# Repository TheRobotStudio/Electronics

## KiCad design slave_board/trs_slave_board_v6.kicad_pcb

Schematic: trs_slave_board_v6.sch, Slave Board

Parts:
C1: 10µF
C2: C
CAN_Transceiver1: SN65HVD232D
K1: CONN_3
MASTER_EPOS2_1: Headers_CONN
MBED_SB_1: mbed_NXP_LPC1768
MUX_1: MUX_CD74HC4067
P1, P2, P6: CONN_4
P3, P4: CONN_6
P5: CONN_10
P7: CONN_8X2
P8, P9: CONN_1
R1: 120
R2: R

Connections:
GND: C1.2, C2.2, CAN_Transceiver1.2, CAN_Transceiver1.8, K1.3, MASTER_EPOS2_1.2, MASTER_EPOS2_1.8, MBED_SB_1.1, MUX_1.12 (GND), P1.1, P1.2, P1.3, P1.4, R2.2
unnamed: MUX_1.4 (CHAN5), P7.6
unnamed: MUX_1.2 (CHAN7), P7.8
unnamed: MUX_1.3 (CHAN6), P7.7
unnamed: MUX_1.5 (CHAN4), P7.5
unnamed: MUX_1.6 (CHAN3), P7.4
unnamed: MUX_1.7 (CHAN2), P7.3
unnamed: MUX_1.22 (CHAN9), P7.10
unnamed: MUX_1.19 (CHAN12), P7.13
unnamed: MUX_1.20 (CHAN11), P7.12
unnamed: MUX_1.21 (CHAN10), P7.11
unnamed: MUX_1.23 (CHAN8), P7.9
unnamed: MBED_SB_1.24, P5.7
unnamed: MBED_SB_1.36, P4.1
unnamed: MBED_SB_1.35, P4.2
unnamed: MBED_SB_1.34, P4.3
unnamed: MBED_SB_1.33, P4.4
unnamed: MBED_SB_1.32, P4.5
unnamed: MBED_SB_1.31, P4.6
unnamed: MBED_SB_1.21, P5.10
unnamed: MBED_SB_1.22, P5.9
unnamed: MBED_SB_1.23, P5.8
unnamed: MBED_SB_1.25, P5.6
unnamed: MBED_SB_1.26, P5.5
unnamed: MUX_1.8 (CHAN1), P7.2
unnamed: MUX_1.9 (CHAN0), P7.1
unnamed: MBED_SB_1.12, P8.1
unnamed: MBED_SB_1.29, MUX_1.11 (S1), P5.2
unnamed: MBED_SB_1.30, MUX_1.10 (S0), P5.1
unnamed: K1.2 (PM), MBED_SB_1.14
unnamed: K1.1, MBED_SB_1.13
unnamed: MUX_1.15 (EN), R2.1
unnamed: MBED_SB_1.27, MUX_1.13 (S3), P5.4
unnamed: MBED_SB_1.28, MUX_1.14 (S2), P5.3
unnamed: MUX_1.16 (CHAN15), P7.16
unnamed: MBED_SB_1.20, P3.6
unnamed: MBED_SB_1.19, P3.5
unnamed: MBED_SB_1.18, P3.4
unnamed: MBED_SB_1.17, P3.3
unnamed: MBED_SB_1.16, P3.2
unnamed: MUX_1.17 (CHAN14), P7.15
unnamed: MUX_1.18 (CHAN13), P7.14
unnamed: MBED_SB_1.15, MUX_1.1 (COM), P3.1
unnamed: MBED_SB_1.39, P9.1
unnamed: CAN_Transceiver1.1, MBED_SB_1.10
unnamed: CAN_Transceiver1.4, MBED_SB_1.9
unnamed: MASTER_EPOS2_1.4, MBED_SB_1.8
unnamed: MASTER_EPOS2_1.7, MBED_SB_1.7
unnamed: MASTER_EPOS2_1.5, MBED_SB_1.6
unnamed: CAN_Transceiver1.6, MASTER_EPOS2_1.10, R1.1
unnamed: MASTER_EPOS2_1.6, MBED_SB_1.11
unnamed: CAN_Transceiver1.7, MASTER_EPOS2_1.9, R1.2
unnamed: C2.1, CAN_Transceiver1.3, MBED_SB_1.40, MUX_1.24 (VCC), P6.1, P6.2, P6.3, P6.4
unnamed: MASTER_EPOS2_1.3, MBED_SB_1.5
unnamed: C1.1, MASTER_EPOS2_1.1, MBED_SB_1.2, P2.1, P2.2, P2.3, P2.4

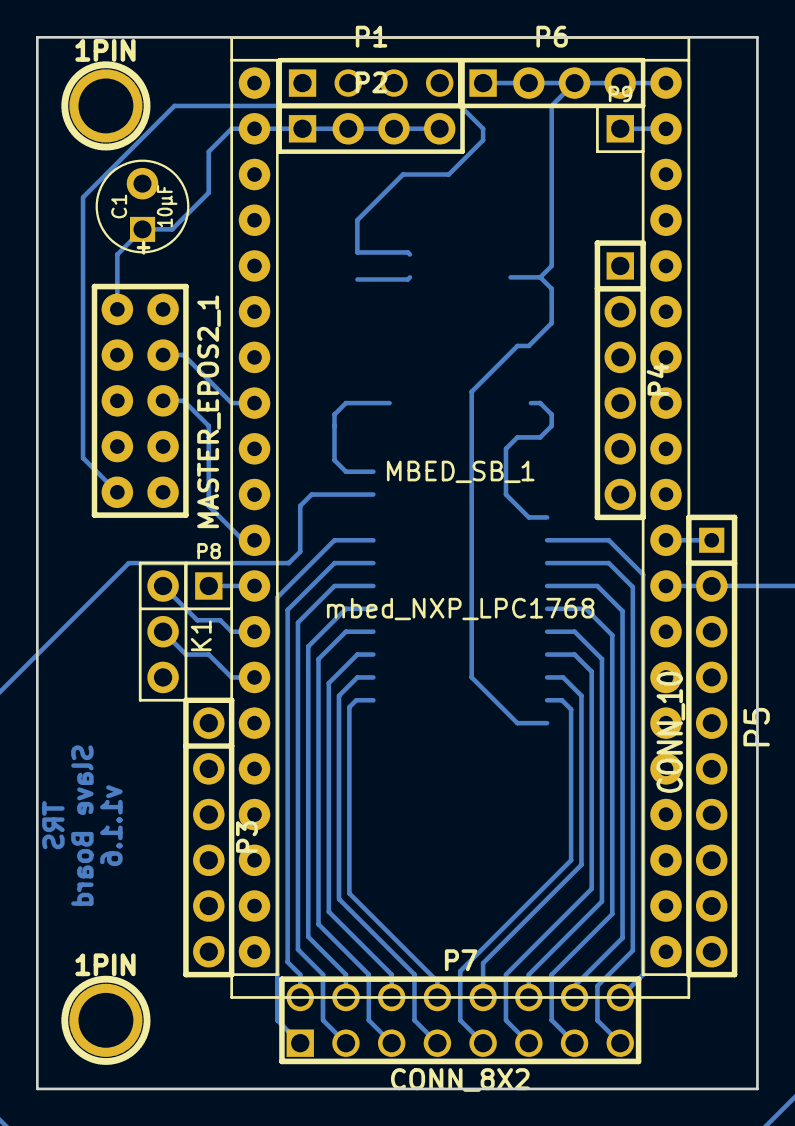
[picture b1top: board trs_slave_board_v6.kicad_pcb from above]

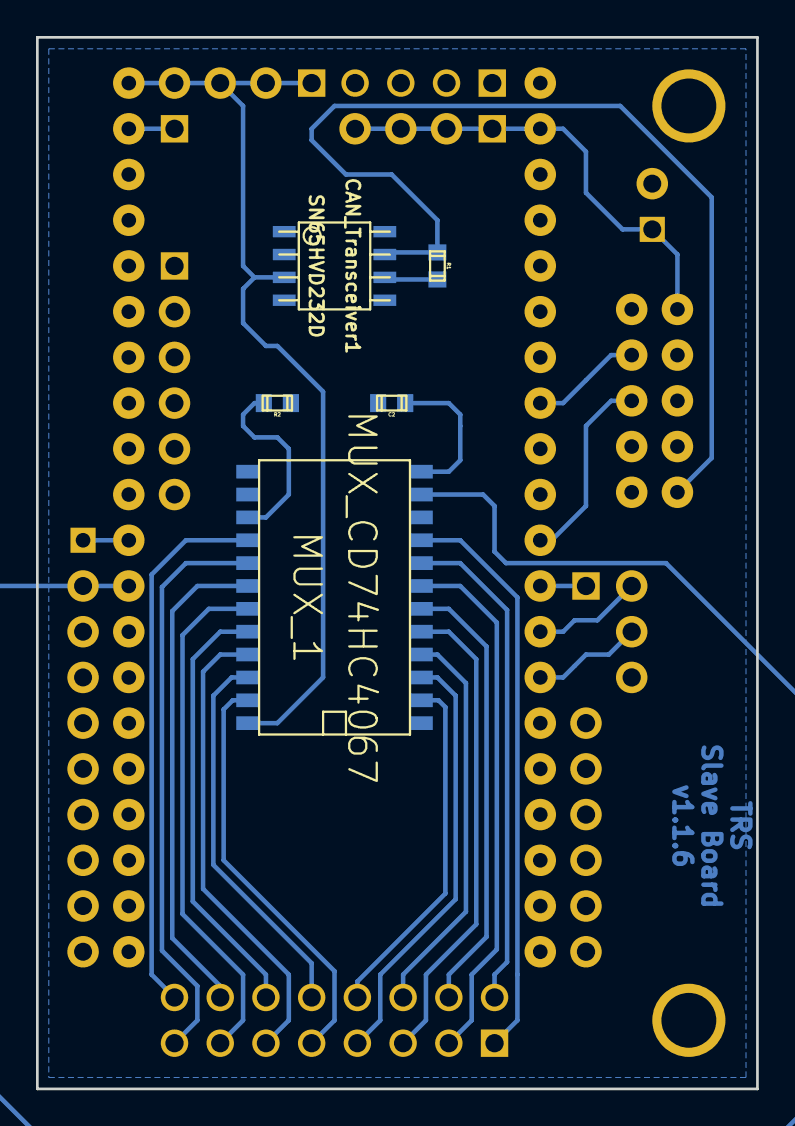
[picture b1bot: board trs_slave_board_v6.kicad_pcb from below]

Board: 2 copper layers, 40.0 x 58.4 mm, 20 parts (5 on the bottom side), 55 nets.

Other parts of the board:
1PIN, 1PIN#2: P***; 1pin

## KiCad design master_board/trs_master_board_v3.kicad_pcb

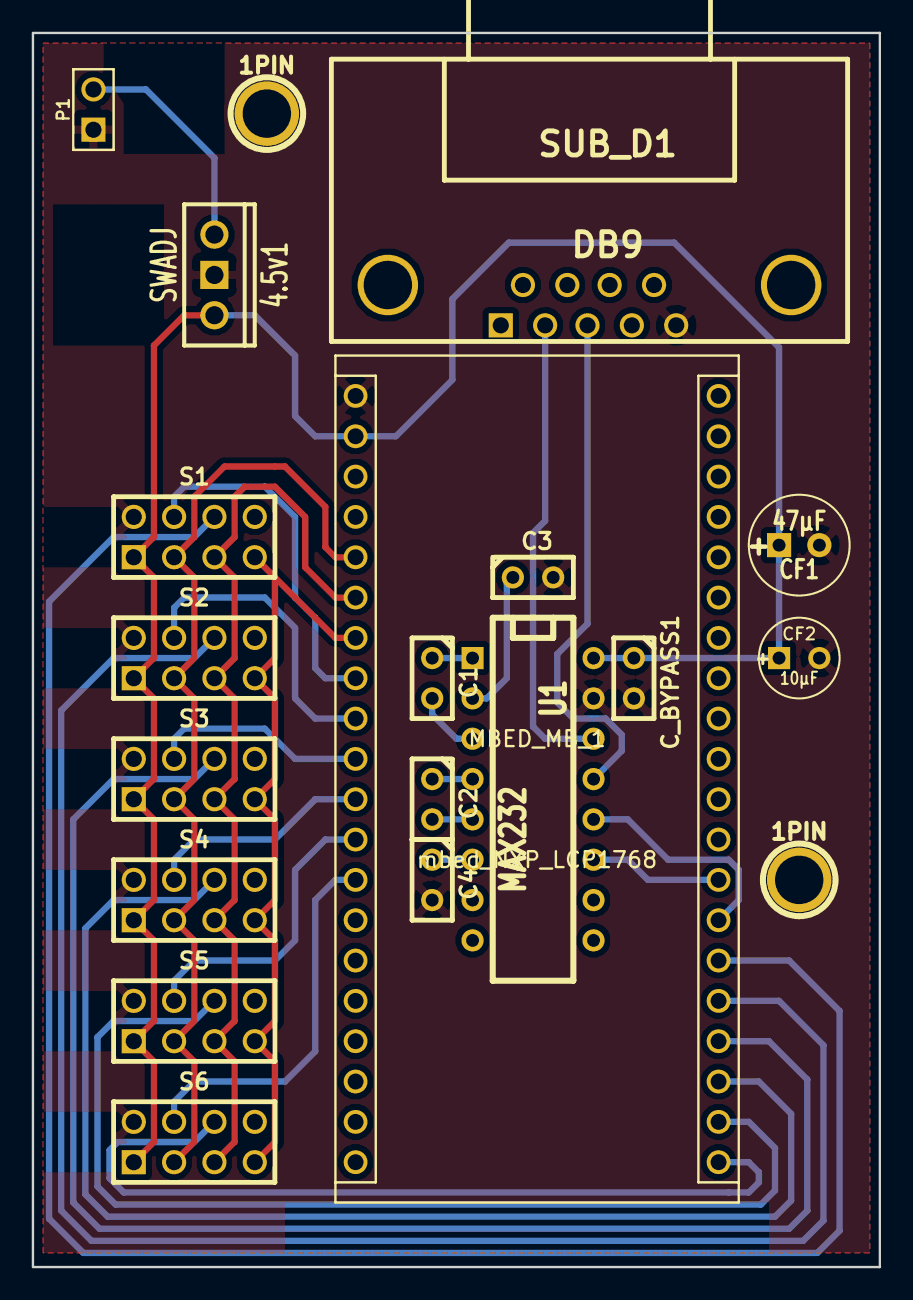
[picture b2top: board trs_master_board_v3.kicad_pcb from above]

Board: 2 copper layers, 53.3 x 77.7 mm, 20 parts (0 on the bottom side), 28 nets.

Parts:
1PIN, 1PIN#2: P***; 1pin
4.5v1: SWADJ; LM78XXV
C1, C2: 1µF; C1
C3, C4: 100 nF; C1
CF1: 47µF; C1V7
CF2: 10µF; C1V5
C_BYPASS1: 100 nF; C1
MBED_MB_1: mbed_NXP_LCP1768; Mbed
P1: CONN_2; PIN_ARRAY_2X1
S1, S2, S3, S4, S5, S6: SLAVE_CONN; pin_array_4x2
SUB_D1: DB9; DB9FC
U1: MAX232; DIP-16__300

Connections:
GND: 4.5v1.GND, C3.2, C4.2, CF1.2, CF2.2, C_BYPASS1.2, MBED_MB_1.1, P1.1, S1.2, S2.2, S3.2, S4.2, S5.2, S6.2, SUB_D1.5, U1.15
unnamed: SUB_D1.3, U1.13
unnamed: MBED_MB_1.13, S6.4
unnamed: SUB_D1.2, U1.14
unnamed: MBED_MB_1.28, U1.11
unnamed: MBED_MB_1.27, U1.12
unnamed: MBED_MB_1.8, S1.4
unnamed: MBED_MB_1.6, S1.5, S2.5, S3.5, S4.5, S5.5, S6.5
unnamed: MBED_MB_1.24, S3.6
unnamed: MBED_MB_1.21, S6.6
unnamed: MBED_MB_1.22, S5.6
unnamed: MBED_MB_1.23, S4.6
unnamed: MBED_MB_1.25, S2.6
unnamed: MBED_MB_1.26, S1.6
unnamed: MBED_MB_1.12, S5.4
unnamed: MBED_MB_1.11, S4.4
unnamed: MBED_MB_1.7, S1.7, S2.7, S3.7, S4.7, S5.7, S6.7
unnamed: 4.5v1.VI, P1.2
unnamed: MBED_MB_1.5, S1.3, S2.3, S3.3, S4.3, S5.3, S6.3
unnamed: C4.1, U1.6
unnamed: C3.1, U1.2
unnamed: C2.2, U1.5
unnamed: C2.1, U1.4
unnamed: C1.2, U1.3
unnamed: C1.1, U1.1
unnamed: MBED_MB_1.9, S2.4
unnamed: 4.5v1.VO, CF1.1, CF2.1, C_BYPASS1.1, MBED_MB_1.2, S1.1, S2.1, S3.1, S4.1, S5.1, S6.1, U1.16
unnamed: MBED_MB_1.10, S3.4

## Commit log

2015-02-13 v1.0.0
2015-02-13 v1.0.1
2015-11-07 v1.0.2
